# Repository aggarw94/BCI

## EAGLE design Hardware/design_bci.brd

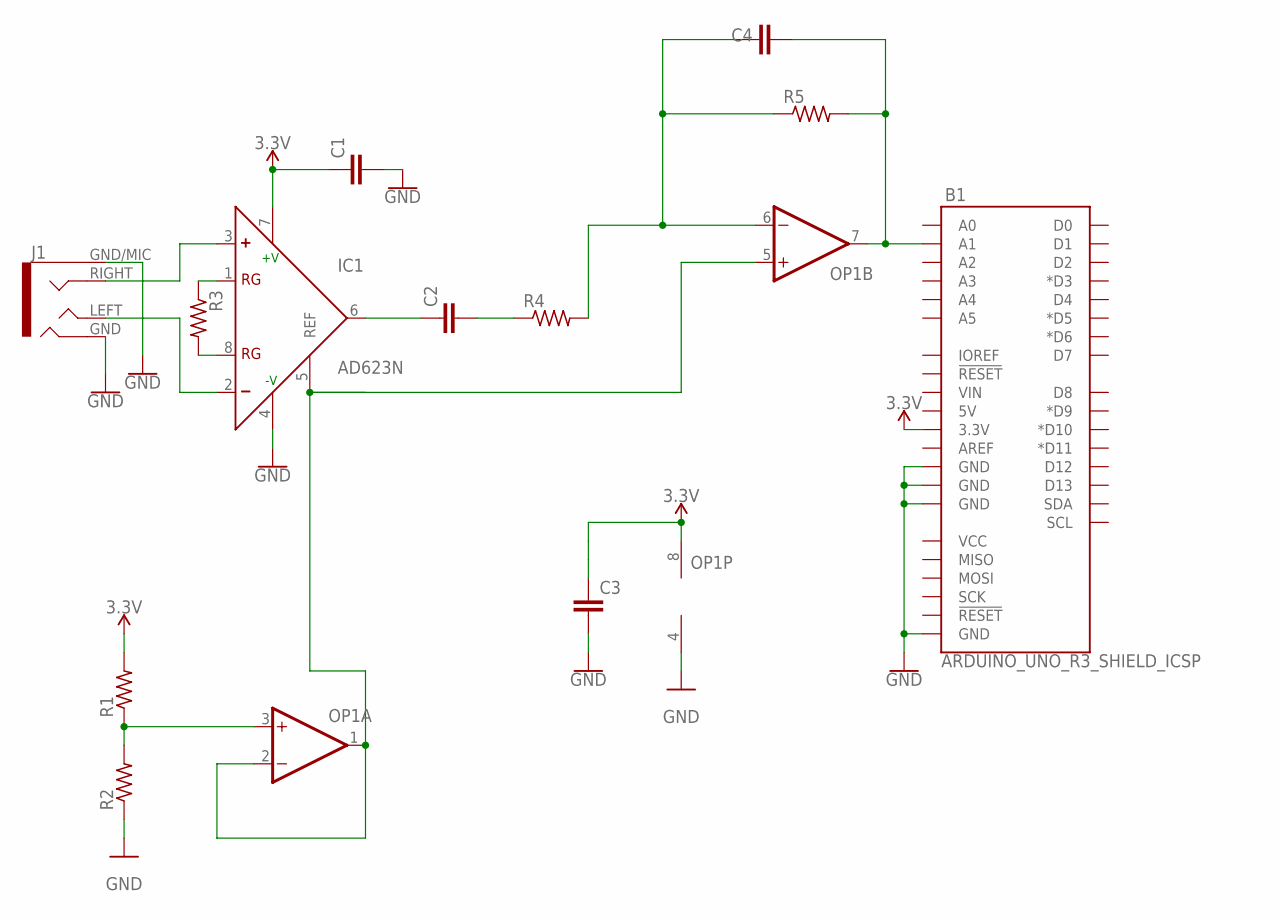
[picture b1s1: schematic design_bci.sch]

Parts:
B1: ARDUINO_UNO_R3_SHIELD_ICSP; UNO_R3_SHIELD_ICSP
C1, C2, C3, C4: CAPACITOR0603; C0603
IC1: AD623N; DIL08
J1: AUDIO_JACK_TRRSSMD_RA; AUDIO_JACK_3.5MM_TRRS_SMD_RA
OP1: OP-DUALMCP6002R; SO8
R1, R2, R3, R4, R5: RESISTOR0603; R0603

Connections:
3.3V: B1.3.3V, C1.1, C3.1, IC1.7 (+V), OP1.8 (V+), R1.2
GND: B1.GND@0 (GND), B1.GND@1 (GND), B1.GND@2 (GND), B1.GND_ICSP (GND), C1.2, C3.2, IC1.4 (-V), J1.GND (RING2), J1.GND/MIC (SLEEVE), OP1.4 (V-), R2.1
unnamed: IC1.8 (RG), R3.2
unnamed: IC1.1 (RG), R3.1
unnamed: OP1.3 (+IN), R1.1, R2.2
unnamed: C2.1, IC1.6 (OUT)
unnamed: C2.2, R4.1
unnamed: IC1.5 (REF), OP1.1 (OUT), OP1.2 (-IN), OP1.5 (+IN)
unnamed: C4.1, OP1.6 (-IN), R4.2, R5.1
unnamed: B1.A1, C4.2, OP1.7 (OUT), R5.2
unnamed: IC1.3 (+), J1.RIGHT (RING1)
unnamed: IC1.2 (-), J1.LEFT (TIP)

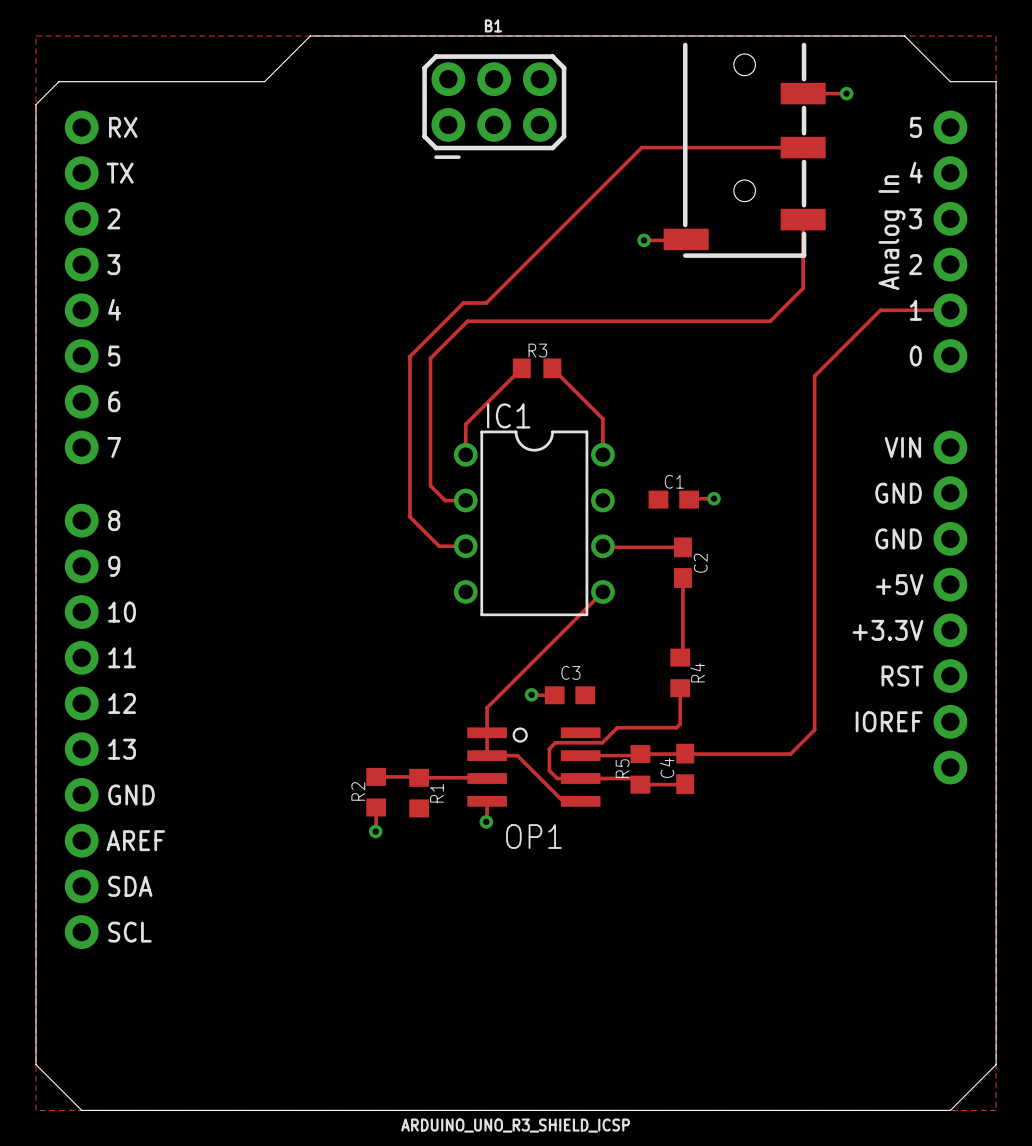
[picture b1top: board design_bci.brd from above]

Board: 2 copper layers, 53.3 x 59.7 mm, 13 parts (0 on the bottom side), 12 nets.

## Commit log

2022-09-15 hardware design
2022-09-21 Hardware
2022-09-21 restored
2022-10-05 made unnoticeable change
2022-11-19 orlando made changes and ordered boards
